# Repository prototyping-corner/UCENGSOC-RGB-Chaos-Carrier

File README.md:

# RGB Chaos Carrier
**WiP - Hopefully this is gone soon**  

## Assembly Instructions
### Kit Contents
Your RGB Chaos Carrier Kit contains:
| Qty | What | Why |
| --- | --- | --- |
| 18 | 180...

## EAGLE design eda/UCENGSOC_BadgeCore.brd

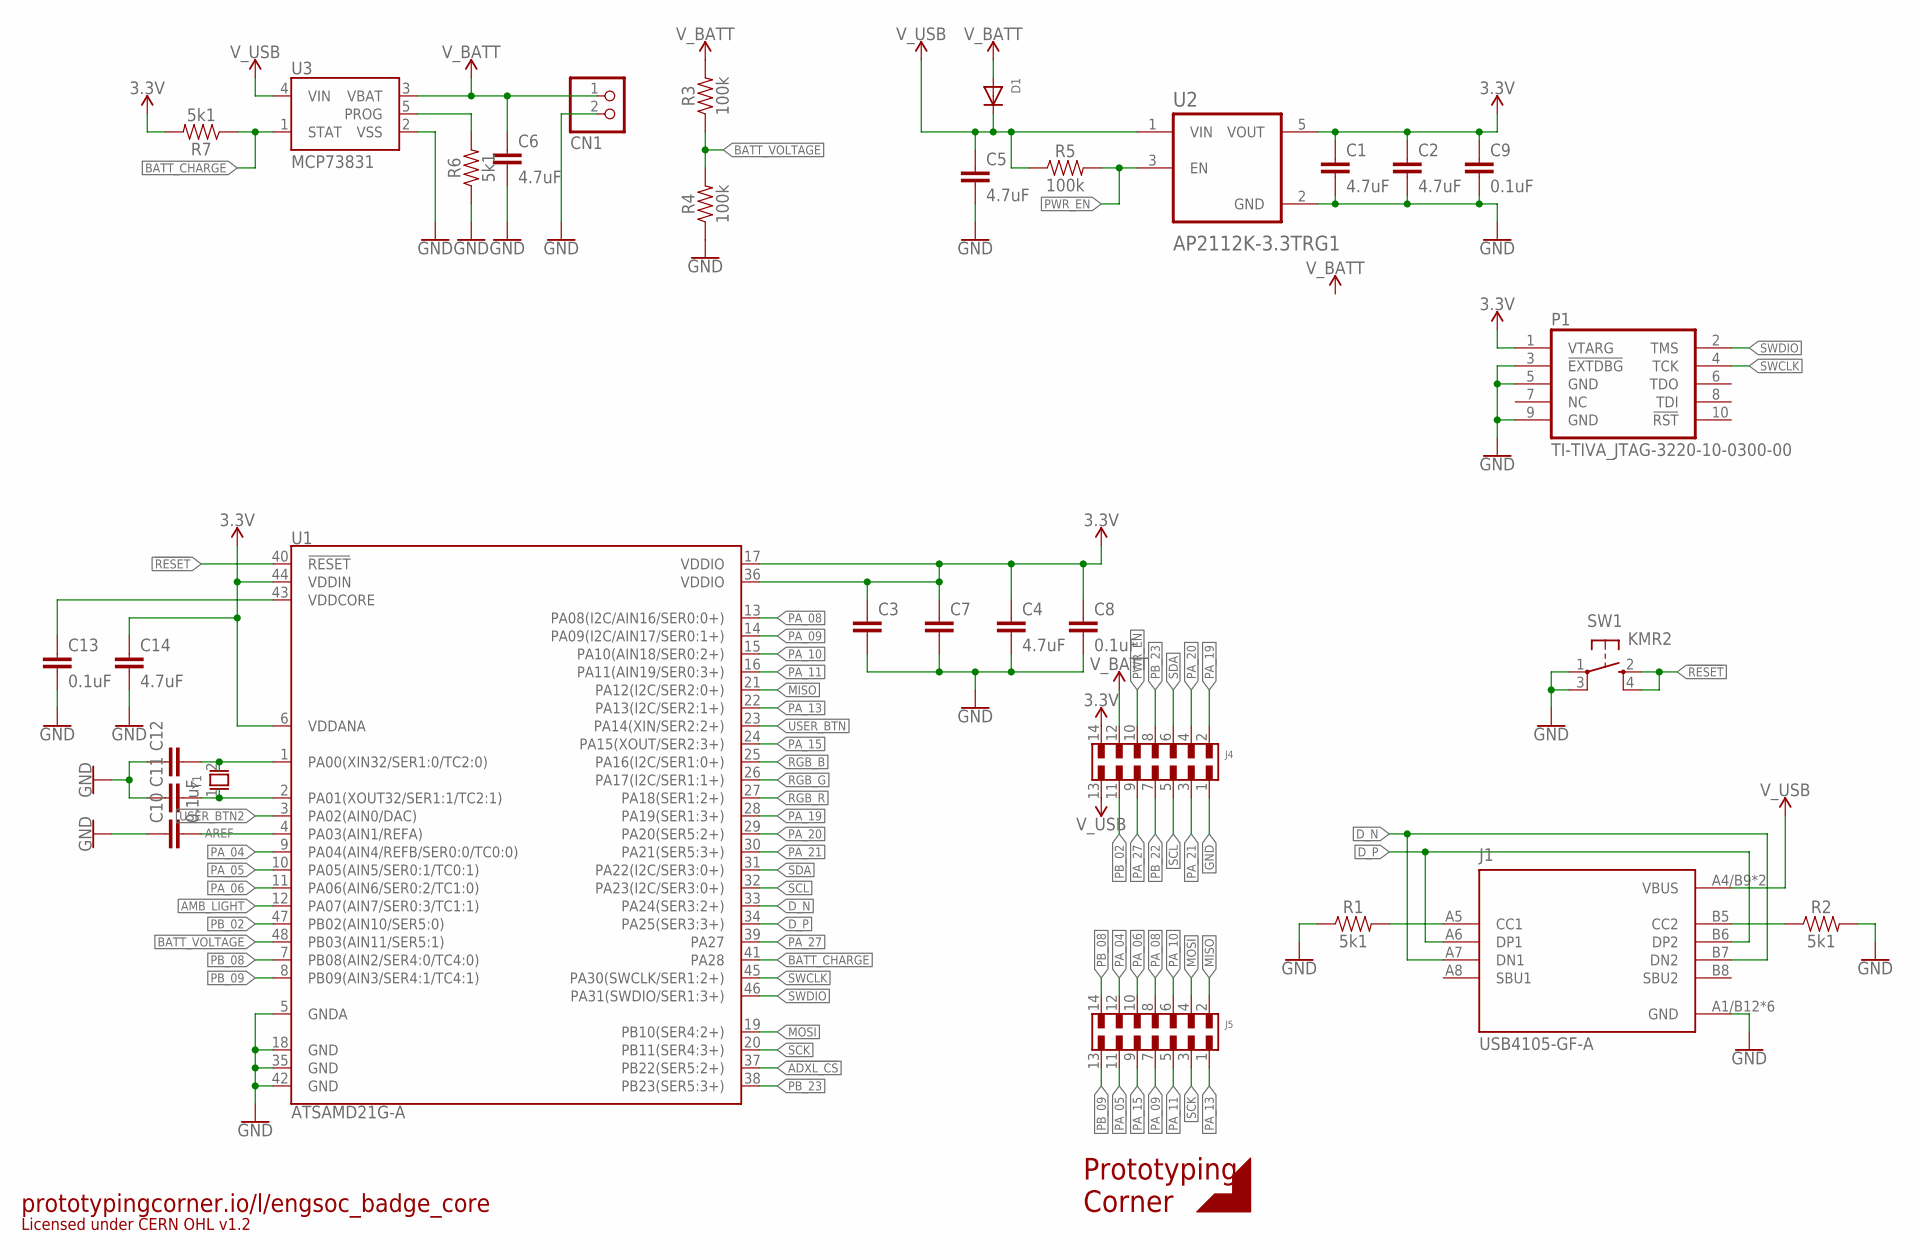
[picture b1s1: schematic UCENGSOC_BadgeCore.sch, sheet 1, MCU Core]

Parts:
C1, C2, C4, C5, C6, C14: 4.7uF; 1206
C3: 4.7UF-1206-16V-(+80/-20%); 1206
C7: 0.1UF-0603-25V-5%; 0603
C8, C9, C10, C13: 0.1uF; 0603
C11, C12: 15PF-0603-50V-5%; 0603
CN1: JST_2PIN-SMT-RA; JST-PH-2-SMT-RA
D1: DIODE_SOD-123FL; SOD-123FL
J1: USB4105-GF-A; GCT_USB4105-GF-A
J4, J5: 6100XX21121_61001421121; 61001421121
P1: TI-TIVA_JTAG-3220-10-0300-00; TI-TIVA_3220-10-0300-00
R1, R2, R6, R7: 5k1; 0603
R3, R4, R5: 100k; 0603
SW1: KMR2
U1: ATSAMD21G-A; TQFP-48
U2: AP2112K-3.3TRG1; SOT95P285X140-5N
U3: MCP73831; SOT23-5
U$1: LOGOSMALL_COPPER; LOGO_SMALL_COPPER
Y1: FC-135_32.7680KA-A0; XTAL_FC-135_32.7680KA-A0

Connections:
3.3V: C1.1, C2.1, C3.1, C4.1, C7.1, C8.1, C9.1, C14.1, J4.14, P1.1 (VTARG), R7.2, U1.6 (VDDANA), U1.17 (VDDIO), U1.36 (VDDIO), U1.44 (VDDIN), U2.5 (VOUT); also elsewhere on the board
!ADXL_CS: U1.37 (PB22(SER5:2+)); also elsewhere on the board
!RESET: SW1.2 (S), SW1.4 (S1), U1.40 (!RESET!)
AMB_LIGHT: U1.12 (PA07(AIN7/SER0:3/TC1:1)); also elsewhere on the board
AREF: C10.2, U1.4 (PA03(AIN1/REFA))
BATT_CHARGE: R7.1, U1.41 (PA28), U3.1 (STAT)
BATT_VOLTAGE: R3.1, R4.2, U1.48 (PB03(AIN11/SER5:1))
D_N: J1.A7 (DN1), J1.B7 (DN2), U1.33 (PA24(SER3:2+))
D_P: J1.A6 (DP1), J1.B6 (DP2), U1.34 (PA25(SER3:3+))
GND: C1.2, C2.2, C3.2, C4.2, C5.2, C6.2, C7.2, C8.2, C9.2, C10.1, C11.1, C12.1, C13.2, C14.2, CN1.2 (1), J1.A1/B12 (GND), J1.B1/A12 (GND), J1.G1 (GND), J1.G2 (GND), J1.G3 (GND), J1.G4 (GND), J4.1, P1.3 (!EXTDBG!), P1.5 (GND), P1.9 (GND), R1.1, R2.2, R4.1, R6.1, SW1.1, SW1.3 (P1), U1.5 (GNDA), U1.18 (GND), U1.35 (GND), U1.42 (GND), U2.2 (GND), U3.2 (VSS); also elsewhere on the board
MISO: J5.2, U1.21 (PA12(I2C/SER2:0+)); also elsewhere on the board
MOSI: J5.4, U1.19 (PB10(SER4:2+)); also elsewhere on the board
unnamed: R6.2, U3.5 (PROG)
unnamed: C13.1, U1.43 (VDDCORE)
unnamed: C12.2, U1.1 (PA00(XIN32/SER1:0/TC2:0)), Y1.2
unnamed: C11.2, U1.2 (PA01(XOUT32/SER1:1/TC2:1)), Y1.1
unnamed: J1.A5 (CC1), R1.2
unnamed: J1.B5 (CC2), R2.1
PA_04: J5.12, U1.9 (PA04(AIN4/REFB/SER0:0/TC0:0))
PA_05: J5.11, U1.10 (PA05(AIN5/SER0:1/TC0:1))
PA_06: J5.10, U1.11 (PA06(AIN6/SER0:2/TC1:0))
PA_08: J5.8, U1.13 (PA08(I2C/AIN16/SER0:0+))
PA_09: J5.7, U1.14 (PA09(I2C/AIN17/SER0:1+))
PA_10: J5.6, U1.15 (PA10(AIN18/SER0:2+))
PA_11: J5.5, U1.16 (PA11(AIN19/SER0:3+))
PA_13: J5.1, U1.22 (PA13(I2C/SER2:1+))
PA_15: J5.9, U1.24 (PA15(XOUT/SER2:3+))
PA_19: J4.2, U1.28 (PA19(SER1:3+))
PA_20: J4.4, U1.29 (PA20(SER5:2+))
PA_21: J4.3, U1.30 (PA21(SER5:3+))
PA_27: J4.9, U1.39 (PA27)
PB_02: J4.11, U1.47 (PB02(AIN10/SER5:0))
PB_08: J5.14, U1.7 (PB08(AIN2/SER4:0/TC4:0))
PB_09: J5.13, U1.8 (PB09(AIN3/SER4:1/TC4:1))
PB_22: J4.7
PB_23: J4.8, U1.38 (PB23(SER5:3+))
PWR_EN: J4.10, R5.2, U2.3 (EN)
RGB_B: U1.25 (PA16(I2C/SER1:0+)); also elsewhere on the board
RGB_G: U1.26 (PA17(I2C/SER1:1+)); also elsewhere on the board
RGB_R: U1.27 (PA18(SER1:2+)); also elsewhere on the board
SCK: J5.3, U1.20 (PB11(SER4:3+)); also elsewhere on the board
SCL: J4.5, U1.32 (PA23(I2C/SER3:0+)); also elsewhere on the board
SDA: J4.6, U1.31 (PA22(I2C/SER3:0+)); also elsewhere on the board
SWCLK: P1.4 (TCK), U1.45 (PA30(SWCLK/SER1:2+))
SWDIO: P1.2 (TMS), U1.46 (PA31(SWDIO/SER1:3+))
USER_BTN: U1.23 (PA14(XIN/SER2:2+)); also elsewhere on the board
USER_BTN2: U1.3 (PA02(AIN0/DAC)); also elsewhere on the board
V_BATT: C6.1, CN1.1 (2), D1.A, J4.12, R3.2, U3.3 (VBAT)
V_USB: C5.1, D1.C, J1.A4/B9 (VBUS), J1.B4/A9 (VBUS), J4.13, R5.1, U2.1 (VIN), U3.4 (VIN)

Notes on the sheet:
prototypingcorner.io/l/engsoc_badge_core
Licensed under CERN OHL v1.2

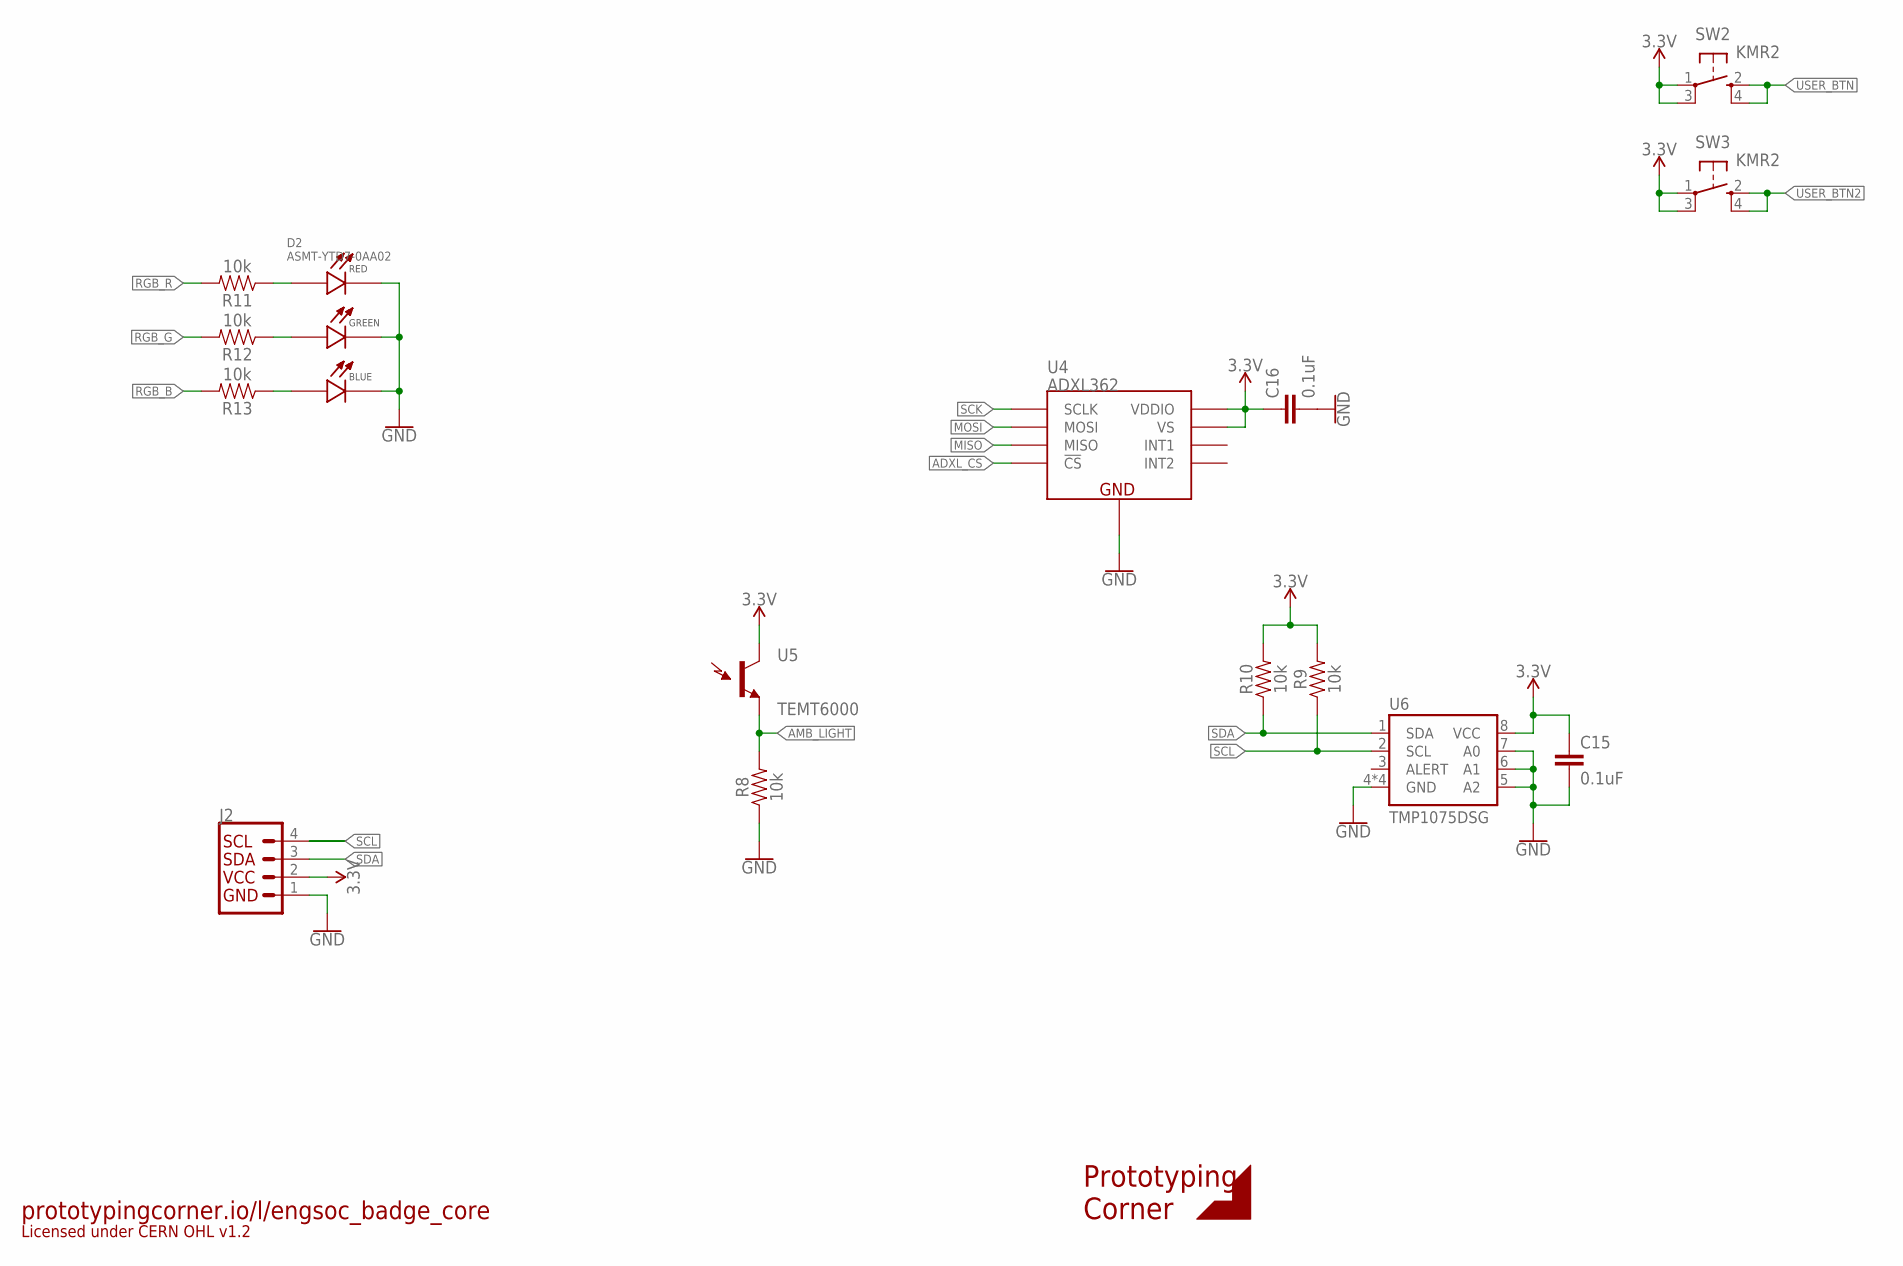
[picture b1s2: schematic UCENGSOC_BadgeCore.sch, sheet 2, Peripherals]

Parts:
C15, C16: 0.1uF; 0603
D2: ASMT-YTD7-0AA02; LED_ASMT-YTD7-0AA02
J2: QWIIC_CONNECTORJS-1MM; 1X04_1MM_RA
R8, R9, R10, R11, R12, R13: 10k; 0603
SW2, SW3: KMR2
U4: ADXL362
U5: TEMT6000; TEMT6000-SEN
U6: TMP1075DSG; WSON8
U$2: LOGOSMALL_COPPER; LOGO_SMALL_COPPER

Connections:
3.3V: C15.1, C16.1, J2.2 (VCC), R9.2, R10.2, SW2.1, SW2.3 (P1), SW3.1, SW3.3 (P1), U4.P$1 (VDDIO), U4.P$14 (VS), U5.COLLECTOR (C1), U6.8 (VCC); also elsewhere on the board
!ADXL_CS: U4.P$8 (!CS); also elsewhere on the board
AMB_LIGHT: R8.2, U5.EMITTER (E1); also elsewhere on the board
GND: C15.2, C16.2, D2.1 (B_C), D2.2 (G_C), D2.3 (R_C), J2.1 (GND), R8.1, U4.P$12 (GND), U4.P$13 (GND), U4.P$16 (GND), U6.4 (GND), U6.5 (A2), U6.6 (A1), U6.7 (A0), U6.9 (GND), U6.10 (GND), U6.11 (GND); also elsewhere on the board
MISO: U4.P$7 (MISO); also elsewhere on the board
MOSI: U4.P$6 (MOSI); also elsewhere on the board
unnamed: D2.6 (B_A), R13.1
unnamed: D2.5 (G_A), R12.1
unnamed: D2.4 (R_A), R11.1
RGB_B: R13.2; also elsewhere on the board
RGB_G: R12.2; also elsewhere on the board
RGB_R: R11.2; also elsewhere on the board
SCK: U4.P$4 (SCLK); also elsewhere on the board
SCL: J2.4 (SCL), R9.1, U6.2 (SCL); also elsewhere on the board
SDA: J2.3 (SDA), R10.1, U6.1 (SDA); also elsewhere on the board
USER_BTN: SW2.2 (S), SW2.4 (S1); also elsewhere on the board
USER_BTN2: SW3.2 (S), SW3.4 (S1); also elsewhere on the board

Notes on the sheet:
prototypingcorner.io/l/engsoc_badge_core
Licensed under CERN OHL v1.2

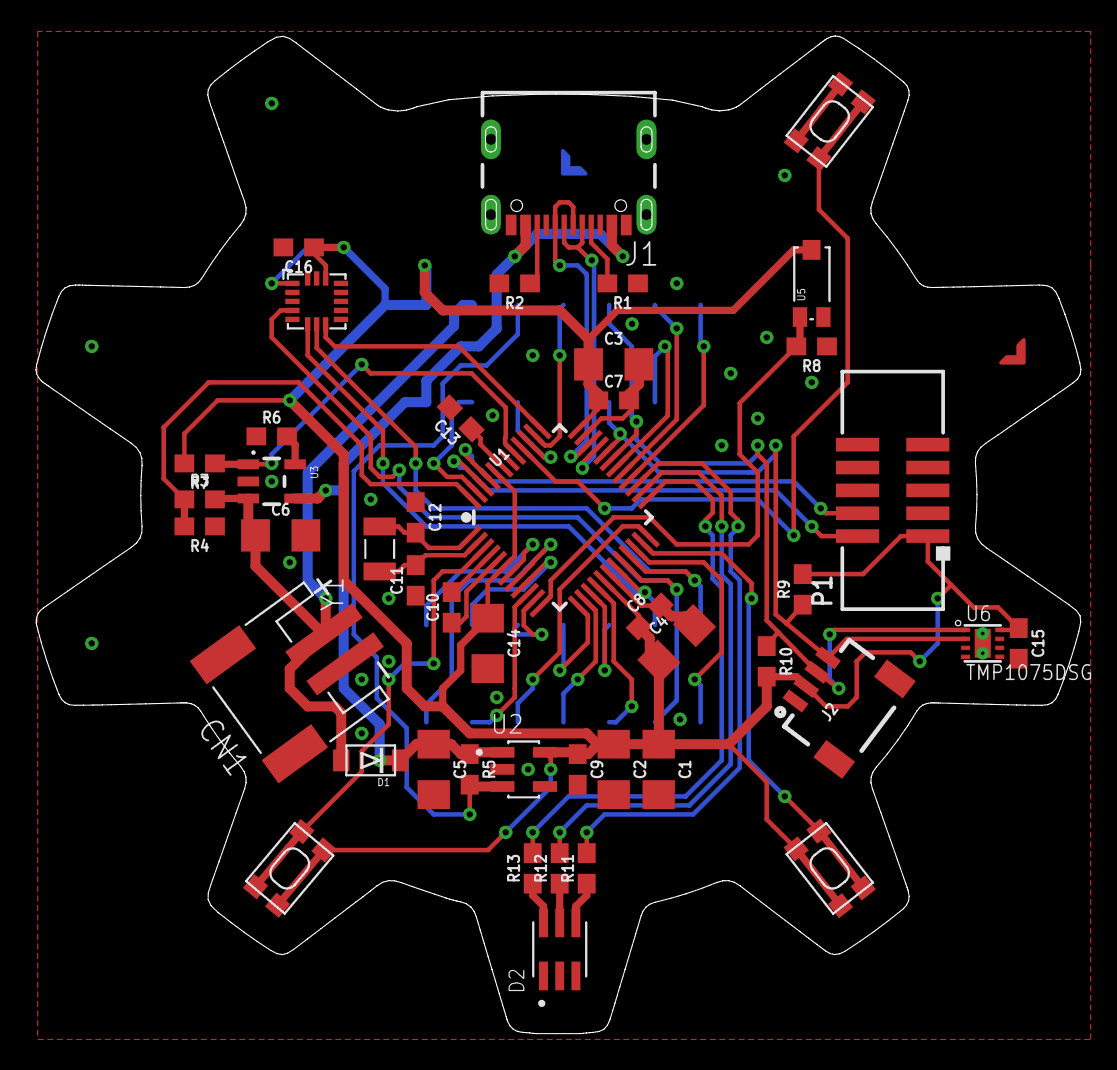
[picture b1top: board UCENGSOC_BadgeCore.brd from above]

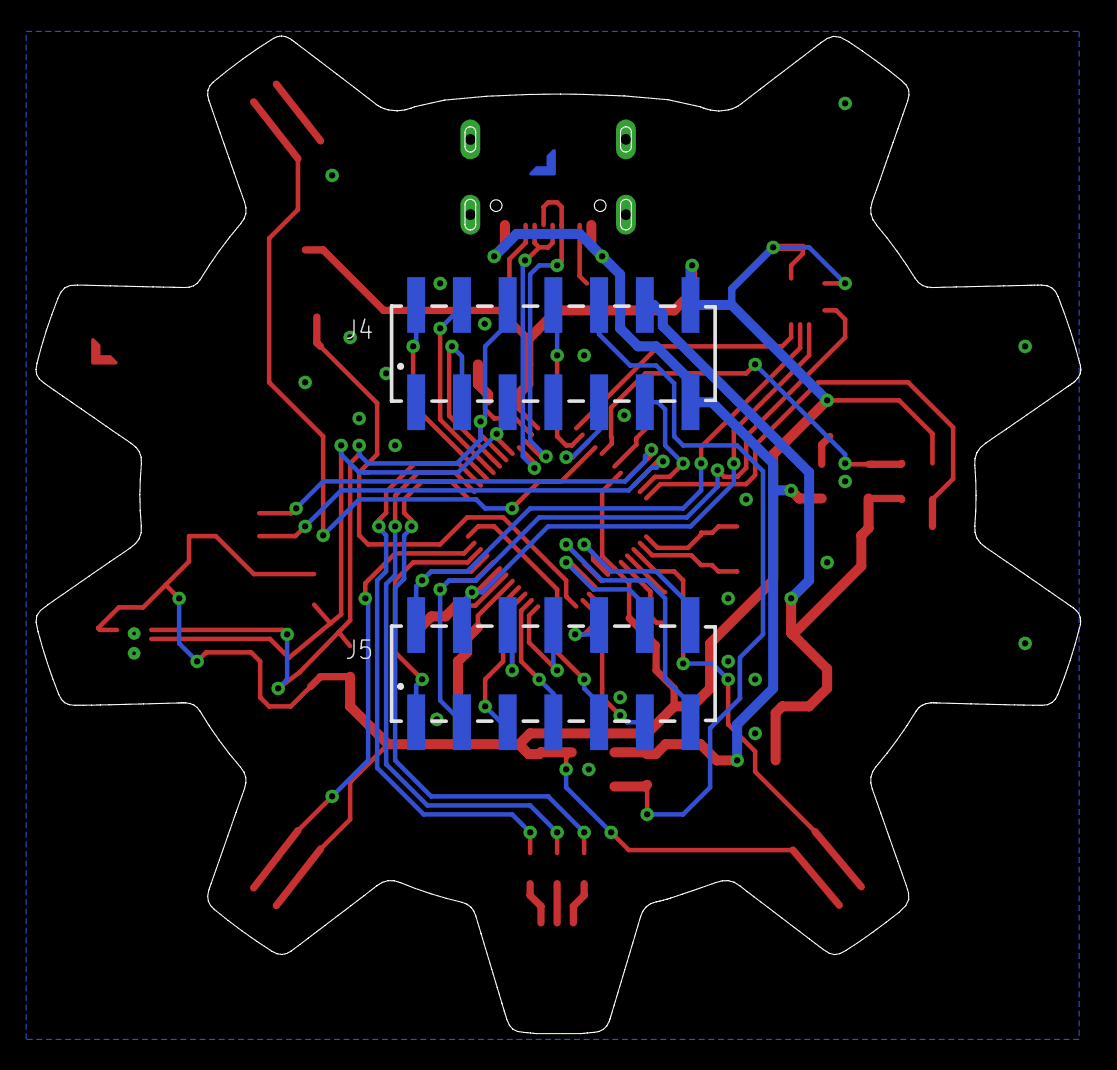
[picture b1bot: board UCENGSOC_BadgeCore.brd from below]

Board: 2 copper layers, 58.0 x 55.4 mm, 49 parts (3 on the bottom side), 51 nets.

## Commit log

2022-04-06 Started Docs
2022-04-06 Presentation
2022-04-07 Woops

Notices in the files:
parts and their libraries:
SparkFun-Capacitors: Licensing: Creative Commons ShareAlike 4.0 International - https://creativecommons.org/licenses/by-sa/4.0
Wurth_Connectors_WR-PHD: Copyright: Würth Elektronik
SparkFun-Sensors: Licensing: CC v3.0 Share-Alike You are welcome to use this library for commercial purposes.
